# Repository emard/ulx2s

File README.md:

# ULX2S board

This project is about to document ULX2S hardware
and hopfully turn it into complete kicad project with
schematics while even improving it.
Currently we have original gerbers pictures and the
[Manual](http://www.nxlab.fer.hr/dl/ulx2s_upute.pdf)
(use google translate).

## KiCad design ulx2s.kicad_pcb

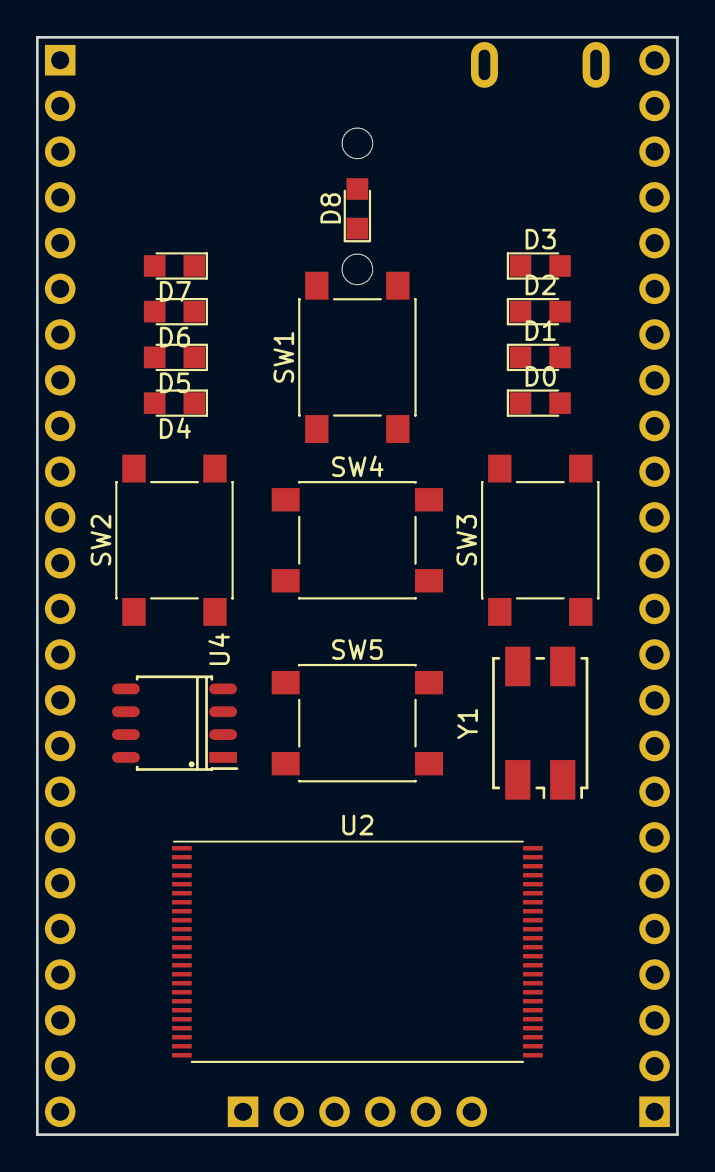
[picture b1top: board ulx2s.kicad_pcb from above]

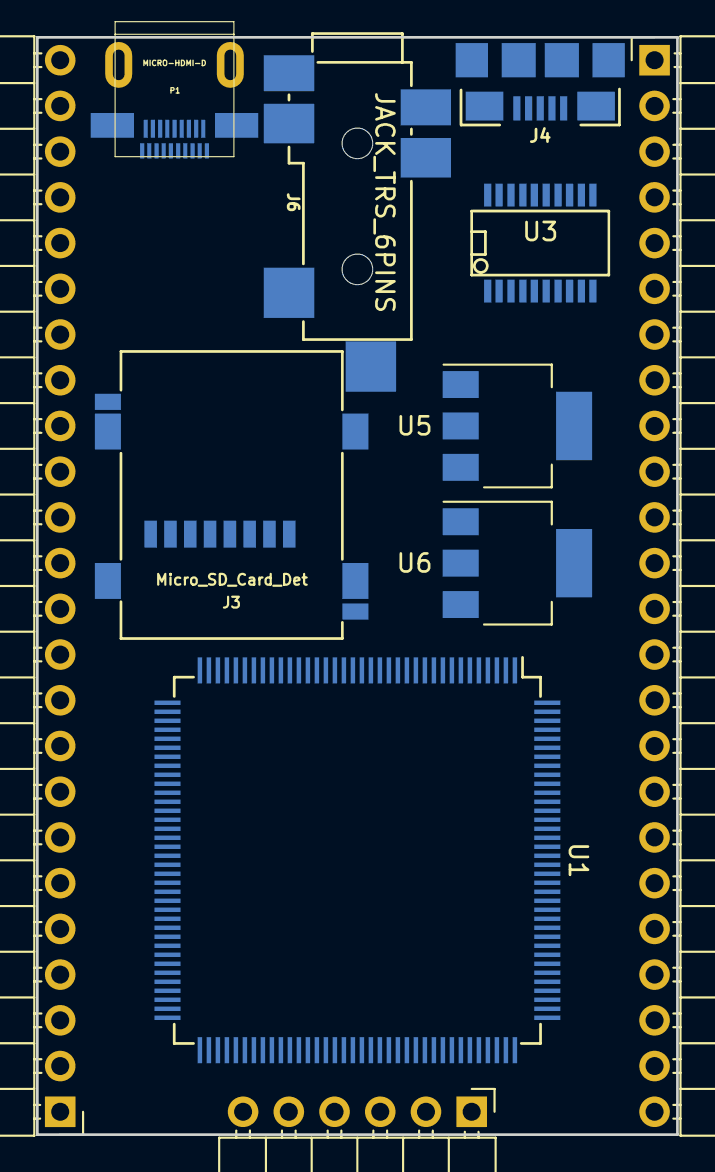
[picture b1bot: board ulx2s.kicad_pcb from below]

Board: 4 copper layers, 35.6 x 61.0 mm, 28 parts (11 on the bottom side), 2 nets, no tracks yet.

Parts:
D0, D1, D2, D3, D4, D5, D6, D7, D8: RED; LED_0805
J1, J2: Conn_01x24; Pin_Header_Angled_1x24_Pitch2.54mm
J3: Micro_SD_Card_Det; SCHD3A100
J4: USB_OTG; USB-MICRO-B-FCI-10118192-0001LF
J5: Conn_01x06; Pin_Header_Angled_1x06_Pitch2.54mm
J6: JACK_TRS_6PINS; CUI_SJ-43516-SMT
P1: MICRO-HDMI-D
SW1, SW2, SW3, SW4, SW5: SW_Push; SW_SPST_PTS645
U1: LFXP2-xE-xTN144x; TQFP-144_20x20mm_Pitch0.5mm
U2: AS6C1616; TSOP-I-48_18.4x12mm_Pitch0.5mm
U3: FT231XS; SSOP-20
U4: SST25VF032B; SOA008-150mil
U5: AZ1117-3.3; SOT-223
U6: AZ1117-1.2; SOT-223
Y1: FNETHE025; Crystal_SMD_7050_4Pads

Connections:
+3V3: J5.1, U2.37, Y1.1, Y1.4
GND: D0.1, D1.1, D2.1, D3.1, D4.1, D5.1, D6.1, D7.1, J3.11, J4.5, J4.6, J5.2, U2.27, U2.46, Y1.2

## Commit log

2017-11-20 gerbers readme
2017-11-20 some footprints collected
2017-11-20 simple kicad project with coarse outline of the board with buttons, 2.54 mm headers, SD card slot, oscillator and USB connector
2017-11-20 readme: link to user's manual PDF
2017-11-20 LEDs
2017-11-20 flash chip
2017-11-20 PCB: oscillator renamed FNETHE025
2017-11-20 "flash" sheet forgotten
2017-11-20 schematic symbol for fpga 144-pin Pins only enumerated, no signal names
2017-11-20 fpga chip placed in the schematic "fpga" sheet and on the PCB.
2017-11-20 SRAM chip (not the correct one AS6C8016 but similar AS6C1616 which was readily available in kicad library)
2017-11-20 usbserial chip ft232rl
2017-11-20 voltage regulators
2017-11-20 footprint audio jack
2017-11-20 audio jack placed
2017-11-20 moving components around to better fit
2017-11-20 micro hdmi connector
2017-11-20 readme update
2017-11-20 usbserial FT232RL changed to FT231XS
2017-11-20 pinout for fpga LFXP2-8E
2017-11-20 footprint fpga pins 1-36 named
2017-11-21 footprint: pins on individual units, not common to all
2017-11-21 some touching, nop changes
2017-11-21 aftertouch
2017-11-21 readme and pic update
2017-11-21 footprint micro hdmi pad SHD->0
2017-11-21 schematics: correct audio jack and return of footprint association for fpga chip
2017-11-21 PCB: update after footprint and schem changes
2017-11-21 schem symbol fpga, cleanup some pins
